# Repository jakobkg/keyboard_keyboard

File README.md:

# The Keyboard Keyboard

A mechanical keyboard with a piano-esque layout, or a MIDI keyboard with MX style switches and (hopefully) QMK firmware?
This is a keyboard design for the very tiny segment of people who think the "computer keyboard as MIDI input" in Ableton is neat, and want more of the same.

PCB design is currently ready for prototyping and hopefully writing firmware, and a basic 3D printed case design will also be added to this repository at some point.
Design files and images will be added as they're ready!

## Firmware
I have been able to make a working firmware with remappable MIDI CC knobs, remappable mod keys, a velocity knob and octave controls.
Analog control of velocity is not currently supported in QMK because of the way it handles velocity in the underlying processing, which I have tried to address with [this pull request](https://github.com/qmk/qmk_firmware/pull/9940). If my changes are merged I will be able to provide firmware through the normal QMK repo, if not I will link my own fork here.

## Images

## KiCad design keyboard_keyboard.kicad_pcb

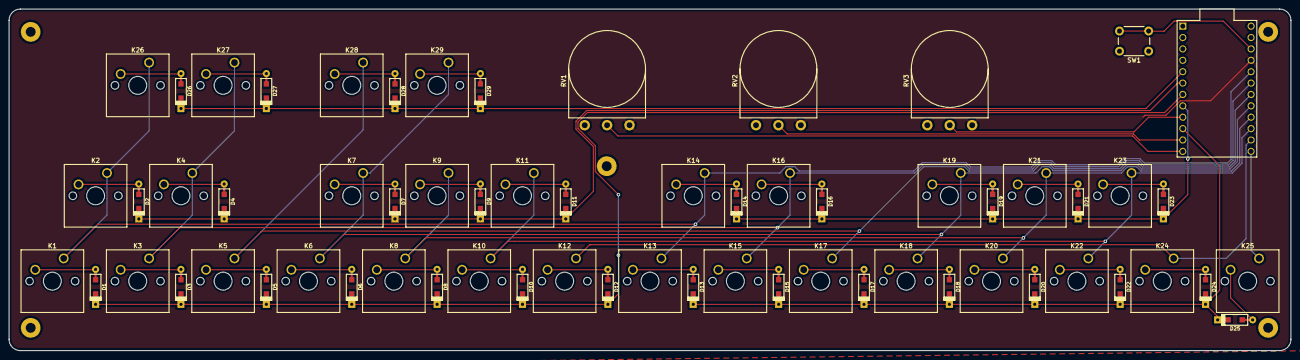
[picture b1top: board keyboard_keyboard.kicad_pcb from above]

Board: 2 copper layers, 286.0 x 76.2 mm, 68 parts (0 on the bottom side), 48 nets.

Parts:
D1, D2, D3, D4, D5, D6, D7, D8, D9, D10, D11, D12, D13, D14, D15, D16, D17, D18, D19, D20, D21, D22, D23, D24, D25, D26, D27, D28, D29: D; D_SOD123_axial
H1, H2, H3, H4, H5: MountingHole; MountingHole_2.2mm_M2_Pad
K1, K2, K3, K4, K5, K6, K7, K8, K9, K10, K11, K12, K13, K14, K15, K16, K17, K18, K19, K20, K21, K22, K23, K24, K25, K26, K27, K28, K29: KEYSW; SW_Cherry_MX_1.00u_PCB
RV1, RV2, RV3: R_POT; Potentiometer_Omeg_PC16BU_Vertical
SW1: SW_PUSH; SW_PUSH_6mm
U1: ProMicro

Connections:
Col1: K1.1, K2.1, K13.1, K14.1, K26.1, U1.20
Col2: K3.1, K4.1, K15.1, K16.1, K27.1, U1.19
Col3: K5.1, K17.1, K28.1, U1.18
Col4: K6.1, K7.1, K18.1, K19.1, K29.1, U1.17
Col5: K8.1, K9.1, K20.1, K21.1, U1.16
Col6: K10.1, K11.1, K22.1, K23.1, U1.15
Col7: K12.1, K24.1, U1.14
Col8: K25.1, U1.13
GND: RV1.3, RV2.3, RV3.3, SW1.1, U1.3, U1.4, U1.23
ModRow: D26.1, D27.1, D28.1, D29.1, U1.5
unnamed: D1.2, K1.2
unnamed: D2.2, K2.2
unnamed: D3.2, K3.2
unnamed: D4.2, K4.2
unnamed: D5.2, K5.2
unnamed: D6.2, K6.2
unnamed: D7.2, K7.2
unnamed: D8.2, K8.2
unnamed: D9.2, K9.2
unnamed: D10.2, K10.2
unnamed: D11.2, K11.2
unnamed: D12.2, K12.2
unnamed: D13.2, K13.2
unnamed: D14.2, K14.2
unnamed: D15.2, K15.2
unnamed: D16.2, K16.2
unnamed: D17.2, K17.2
unnamed: D18.2, K18.2
unnamed: D19.2, K19.2
unnamed: D20.2, K20.2
unnamed: D21.2, K21.2
unnamed: D22.2, K22.2
unnamed: D23.2, K23.2
unnamed: D24.2, K24.2
unnamed: D25.2, K25.2
unnamed: D26.2, K26.2
unnamed: D27.2, K27.2
unnamed: D28.2, K28.2
unnamed: D29.2, K29.2
Pot1: RV1.2, U1.12
Pot2: RV2.2, U1.11
Pot3: RV3.2, U1.9
RESET: SW1.2, U1.22
Row1: D2.1, D4.1, D7.1, D9.1, D11.1, U1.6
Row2: D1.1, D3.1, D5.1, D6.1, D8.1, D10.1, D12.1, U1.7
Row3: D14.1, D16.1, D19.1, D21.1, D23.1, U1.8
Row4: D13.1, D15.1, D17.1, D18.1, D20.1, D22.1, D24.1, D25.1, U1.10
VCC: RV1.1, RV2.1, RV3.1, U1.21

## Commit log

2020-07-16 Initial readme and PCB image
2020-07-16 Update README.md
    oopsed a word
2020-08-17 Second iteration of design
    Still based on the pro micro, but smaller PCB with more knobs and mod keys!
2020-08-17 Remove gerber files from repo
2020-08-18 Remove outdated net file
    Was only needed for autorouting, which I've moved away from
2021-01-17 Add firmware
2021-01-17 oops
2021-01-17 one more
